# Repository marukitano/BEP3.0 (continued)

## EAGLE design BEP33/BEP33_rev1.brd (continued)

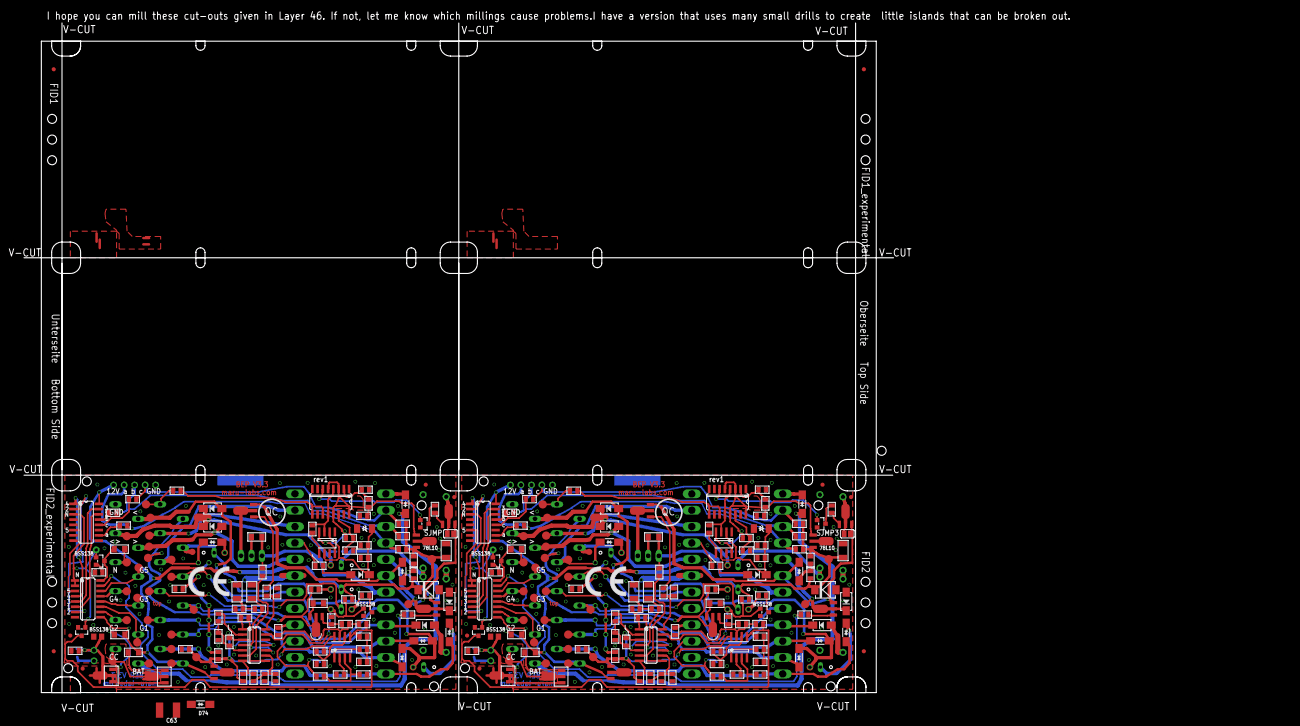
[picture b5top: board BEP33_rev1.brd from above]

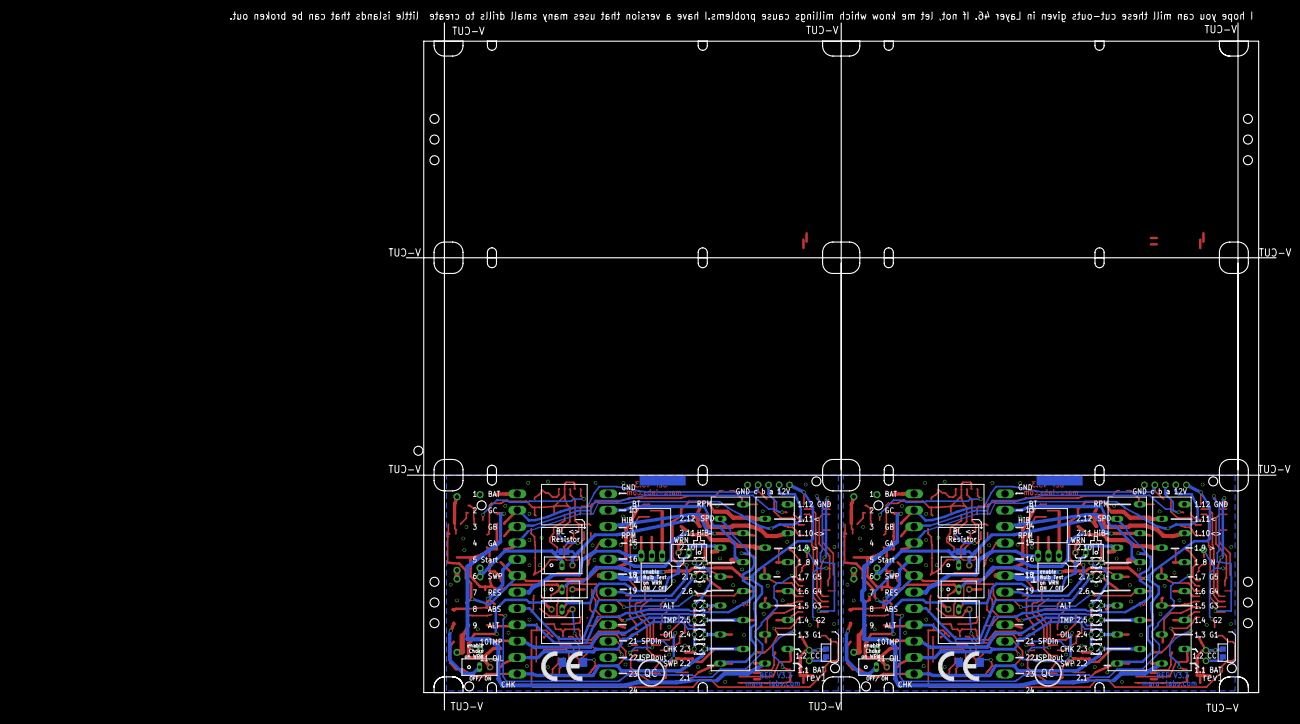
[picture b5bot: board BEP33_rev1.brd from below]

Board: 2 copper layers, 210.4 x 166.2 mm, 306 parts (50 on the bottom side), 181 nets.

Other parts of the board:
U$1, U$2, U$7, U$8: CE_10.00

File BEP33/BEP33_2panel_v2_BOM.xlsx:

Qty | Value | Device | Package | Parts | Description | MF | MPN | OC_FARNELL | OC_NEWARK | TP | TP_SIGNAL_NAME | VALUE
2 | 100nF | CERAMIC-100NF-50V-10%-X7R(0805) | C0805 | C102, C110 | 302010165 |  | CC0805KRX7R9BB104 |  |  |  |  | 10K
2 | 100nF, | CERAMIC-100NF-50V-10%-X7R(0805) | C0805 | C103, C104 | 302010165 |  | CC0805KRX7R9BB104 |  |  |  |  | 100R
2 | 100nF. | CERAMIC-100NF-50V-10%-X7R(0805) | C0805 | C105, C106 | 302010165 |  | CC0805KRX7R9BB104 |  |  |  |  | 2.2K
1 | 2.2nF | CERAMIC-100NF-50V-10%-X7R(0805) | C0805 | C109 | 302010165 |  | CC0805KRX7R9BB104 |  |  |  |  | 220R
2 | 4.7u | CERAMIC-4.7UF-25V-10%-X5R(0805) | C0805 | C15, C101 | 302010146 |  | CC0805KKX5R8BB475 |  |  |  |  | 10K
2 | 100u | CERAMIC-100UF-6.3V-20%-X5R(1206) | C1206 | C107, C108 | 302010183 |  | GRM31CR60J107ME39L |  |  |  |  | 1K
1 | 10u | CERAMIC-100UF-6.3V-20%-X5R(1206) | C1206 | C2 | 302010183 |  | GRM31CR60J107ME39L |  |  |  |  | 4.7K
1 | Zen15 | SM6T | DO214AA | D101 | Z DIODE |  |  |  |  |  |  | 100nf
1 | SM6TDO214AA_BI | SM6TDO214AA_BI | DO214AA_BI | D104 | Z DIODE |  |  |  |  |  |  | 100nf
1 | 1N4007 | DIODE-GEN-PURPOSE-1KV-1A(DO-214AC) | DO-214AC | D112 | 304010013 |  | 1N4007 |  |  |  |  | 100nf
2 | 1N4007, | DIODE-GEN-PURPOSE-1KV-1A(DO-214AC) | DO-214AC | D102, D103 | 304010013 |  | 1N4007 |  |  |  |  | 100uf
2 | 1N4007. | DIODE-GEN-PURPOSE-1KV-1A(DO-214AC) | DO-214AC | D105, D106 | 304010013 |  | 1N4007 |  |  |  |  | 1K
2 | 1N5817 | DIODE-GEN-PURPOSE-1KV-1A(DO-214AC)DO-214AC/1206 | DO-214AC_SLIM | D107, D110 | 304010013 |  |  |  |  |  |  | 220R
2 | 1N5817. | DIODE-GEN-PURPOSE-1KV-1A(DO-214AC)DO-214AC/1206 | DO-214AC_SLIM | D108, D109 | 304010013 |  |  |  |  |  |  | 10K
2 | SS12 | DIODE-GEN-PURPOSE-1KV-1A(DO-214AC)DO-214AC/1206 | DO-214AC_SLIM | D1, D2 | 304010013 |  |  |  |  |  |  | 4.7K
1 | -1000 | SMD-RES-100R-5%-1/8W(0805) | R0805 | R142 | 301010319 |  | RC0805JR-07100RL |  |  |  |  | 1N4007
1 | -1002 | SMD-RES-10K-1%-1/8W(0805) | R0805 | R144 | 301010361 |  | RC0805FR-0710KL |  |  |  |  | 1N4007
1 | -101 | SMD-RES-100R-5%-1/8W(0805) | R0805 | R143 | 301010319 |  | RC0805JR-07100RL
3 | 100 | SMD-RES-2.2K-5%-1/8W(0805) | R0805 | R12, R13, R138 | 301010333 |  | RC0805JR-072K2L
1 | 100 | SMD-RES-220R-5%-1/8W(0805) | R0805 | R4 | 301010315 |  | RC0805JR-07220RL |  |  |  |  | 100nf
5 | 1002 | SMD-RES-10K-1%-1/8W(0805) | R0805 | R107, R108, R120, R124, R132 | 301010361 |  | RC0805FR-0710KL
2 | 1002 | SMD-RES-1K-5%-1/8W(0805) | R0805 | R113, R114 | 301010311 |  | RC0805JR-071KL
1 | 1002 | SMD-RES-4.7K-5%-1/8W(0805) | R0805 | R146 | 301010306 |  | RC0805JR-074K7L |  |  |  |  | 1K
3 | 102 | SMD-RES-1K-5%-1/8W(0805) | R0805 | R101, R112, R128 | 301010311 |  | RC0805JR-071KL |  |  |  |  | 2.2K
1 | 102 | SMD-RES-220R-5%-1/8W(0805) | R0805 | R115 | 301010315 |  | RC0805JR-07220RL |  |  |  |  | 10K
10 | 104 | SMD-RES-10K-1%-1/8W(0805) | R0805 | R1, R2, R3, R109, R110, R111, R125, R130, R135, R141 | 301010361 |  | RC0805FR-0710KL |  |  |  |  | 4.7K
1 | 104 | SMD-RES-4.7K-5%-1/8W(0805) | R0805 | R10 | 301010306 |  | RC0805JR-074K7L
2 | 1502 | SMD-RES-10K-1%-1/8W(0805) | R0805 | R121, R131 | 301010361 |  | RC0805FR-0710KL |  |  |  |  | 4.7uf
1 | 2201 | SMD-RES-1K-5%-1/8W(0805) | R0805 | R6 | 301010311 |  | RC0805JR-071KL
2 | 2201 | SMD-RES-2.2K-5%-1/8W(0805) | R0805 | R119, R133 | 301010333 |  | RC0805JR-072K2L
1 | 2702 | SMD-RES-10K-1%-1/8W(0805) | R0805 | R140 | 301010361 |  | RC0805FR-0710KL
4 | 2702 | SMD-RES-4.7K-5%-1/8W(0805) | R0805 | R117, R122, R123, R145 | 301010306 |  | RC0805JR-074K7L |  |  |  |  | 4.7K
4 | 4701 | SMD-RES-4.7K-5%-1/8W(0805) | R0805 | R8, R105, R116, R126 | 301010306 |  | RC0805JR-074K7L
5 | 13 | SMD-RES-13R-5%-1/4W(1206) | R1206 | R5, R9, R102, R106, R134 | 301010405 |  | RC1206JR-0713RL
1 | 555 | NE555D | SO08 | IC110 | TIMER
1 | LM2904 | LM358D | SO08 | IC101 | OP AMP also LM158; LM258; LM2904
1 | LM339 | LM339D | SO14 | IC108 | Low Power Low Offset Voltage Quad Comparators |  |  |  |  |  |  | BSS138W-7-F
1 | 4028 | 4028D | SO16 | IC105 | BCD to decimal DECODER
1 | 4538 | 4538D | SO16 | IC111 | Dual precision monostable MULTIVIBRATOR
1 | ULN2004 | ULN2004AD | SO16 | IC107 | DRIVER ARRAY
1 | Zen11 | CGRM4001-G | SOD-123_MINI-SMA | D4 | Molded plasitc,JEDEC SOD-123/Mini SMA
4 | J1 | SMD-MOSFET-N-CH-50V-200MA-BSS138W-7-F(SOT-23) | SOT-23 | Q1, Q3, Q106, Q107 | 305030000 |  | BSS138W-7-F
3 | BA | PNP-TRANSISTOR_SOT89 | SOT89 | Q2, Q104, Q105 | PNP TRANSISTOR
2 | BA. | PNP-TRANSISTOR_SOT89 | SOT89 | Q101, Q102 | PNP TRANSISTOR
1 | MY | NPN-TRANSISTOR_SOT89 | SOT89 | Q103 | NPN TRANSISTOR
1 | 78L06 | 78LXXSOT89_ROUND | SOT89_ROUND | IC102
1 | 78L10 | 78LXXSOT89_ROUND | SOT89_ROUND | IC104
1 | 317TO202H_NOHOLE | 317TO202H_NOHOLE | TO220H_NOHOLE | IC109 | Positive VOLTAGE REGULATOR
4 | 47 | R-EU_V235/17_1MM | V235/17_1MM | R127, R129, R136, R137 | RESISTOR, European symbol

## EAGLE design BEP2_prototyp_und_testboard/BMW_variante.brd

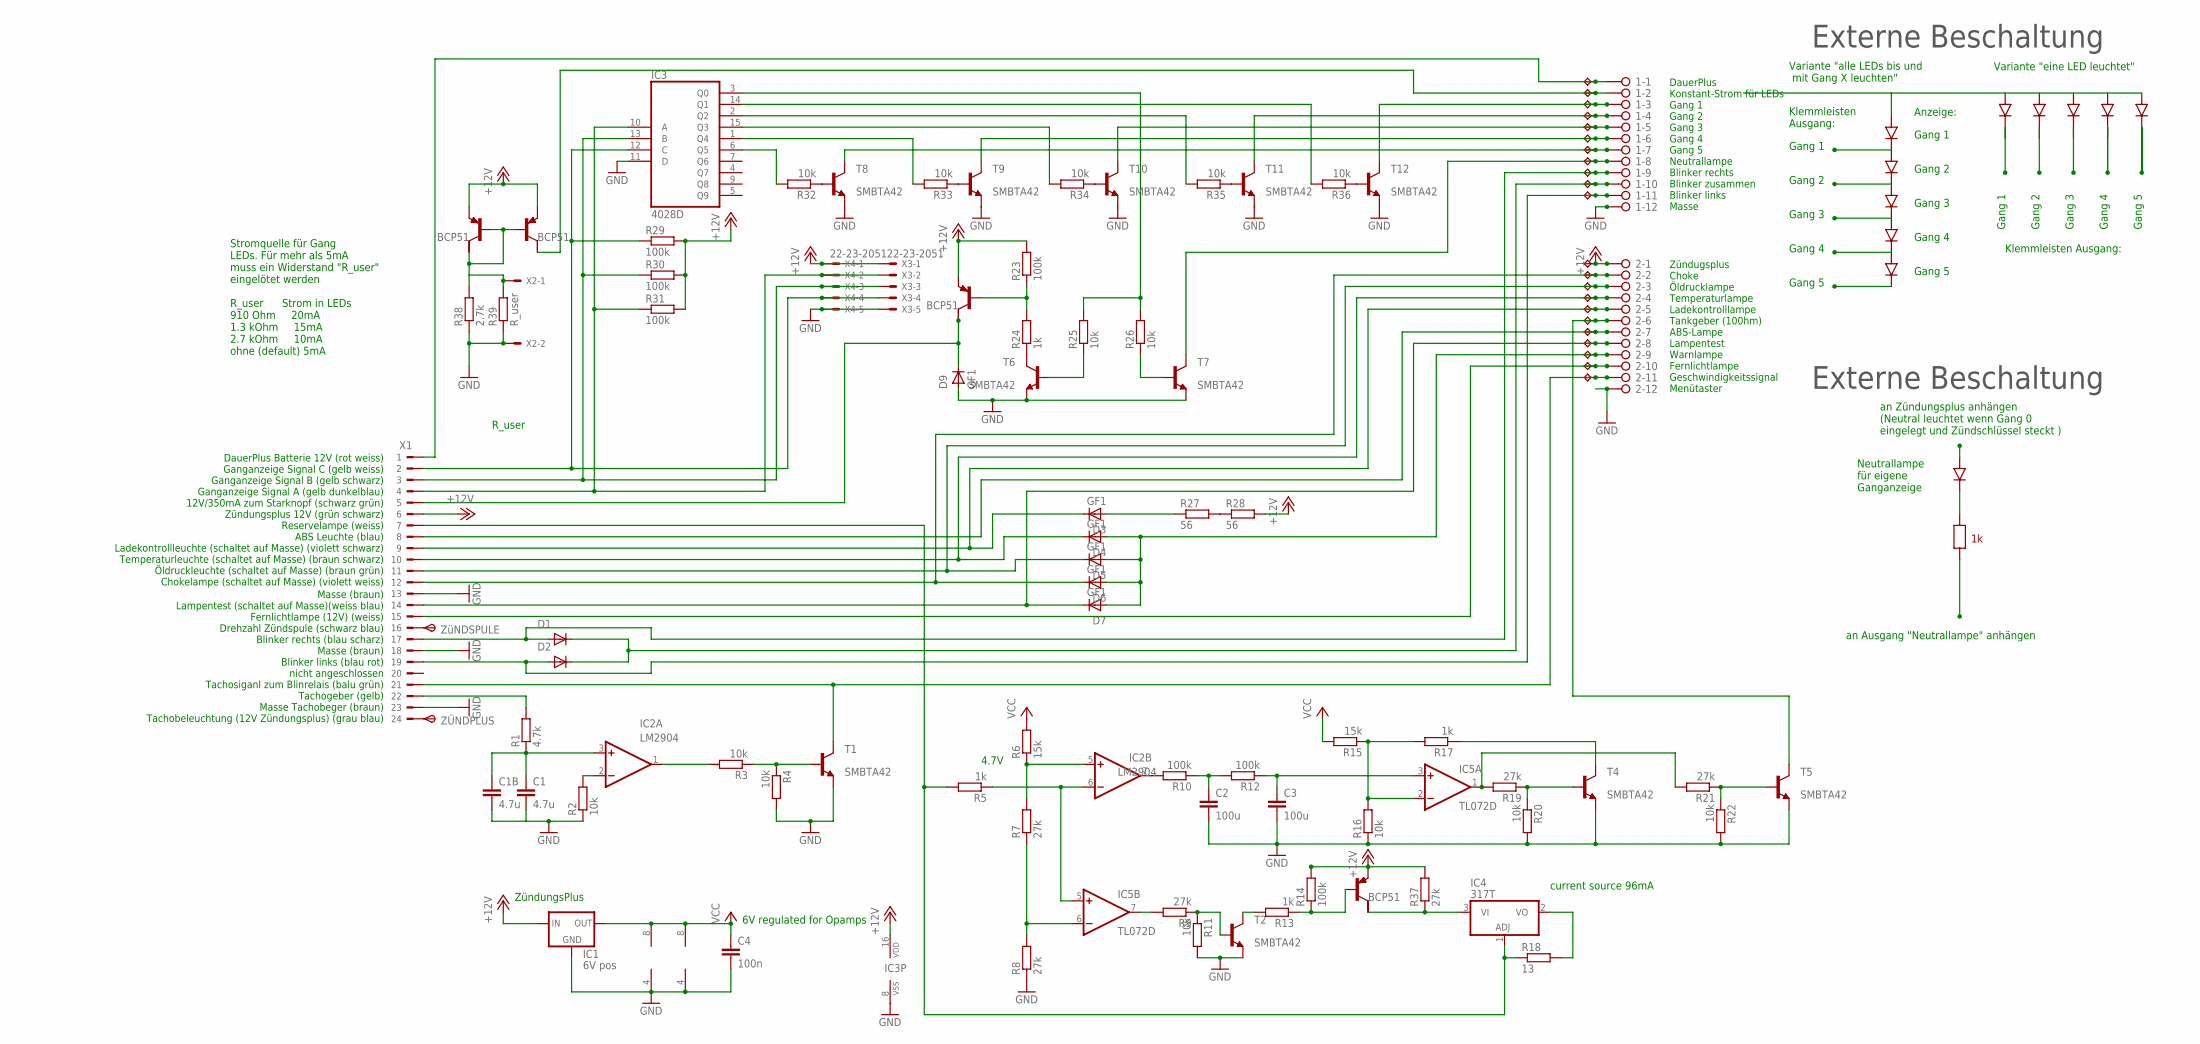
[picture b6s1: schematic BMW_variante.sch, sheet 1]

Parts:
1, 2: 2081-1132; 12-PIN
C1: 4.7u; C1206
C1B: 4.7u; C0805K
C2, C3: 100u; C1206K
C4: 100n; C1206K
D1, D2, D3, D4, D5, D6, D7, D9: GF1; SMA-DO214AC
IC1: 6V pos; 78LXX
IC2: LM358D; SO08
IC3: 4028D; SO16
IC4: 317T; TO220H
IC5: TL072D; SO08
R1: 4.7k; R0805
R2, R3, R4, R11, R16, R20, R22, R25, R26, R32, R33, R34, R35, R36: 10k; R0805
R5, R13, R17, R24: 1k; R0805
R6, R15: 15k; R0805
R7, R8, R9, R19, R21, R37: 27k; R0805
R10, R12, R14, R23, R29, R30, R31: 100k; R0805
R18: 13; 0207/10
R27, R28: 56; V235/17
R38: 2.7k; R0805
R39: R_user; R0805
T, T3, T13, T14: BCP53T1; SOT223
T1, T2, T4, T5, T6, T7, T8, T9, T10, T11, T12: MMBTA42LT1-NPN-SOT23-BEC; SOT23-BEC
TP1, TP2, TP3, TP4, TP5, TP6, TP7, TP8, TP9, TP10, TP11, TP12, TP16, TP17, TP18, TP19, TP21, TP22, TP23, TP24, TP25, TP26: TPB1,27; B1,27
X1: CON_BMW; 24-PIN
X2: 22-23-2021
X3, X4: 22-23-2051
ZÜNDPLUS: TPSP1_1MM; P1_1.0MM
ZüNDSPULE: TPSP1_1MM; P1_1.0MM

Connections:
+12V: 2.1, IC1.IN, IC3.16 (VDD), R14.2, R23.2, R28.2, R29.2, R30.2, R31.2, R37.2, T.3 (E), T3.3 (E), T13.3 (E), T14.3 (E), TP12.TP, X1.6, X3.1, X4.1
GND: 1.12, 2.12, C1.2, C1B.2, C2.2, C3.2, C4.2, D9.A, IC1.GND, IC2.4 (V-), IC3.8 (VSS), IC3.11 (D), IC5.4 (V-), R2.1, R4.2, R8.1, R11.2, R16.1, R20.2, R22.2, R38.1, R39.1, T1.E, T2.E, T4.E, T5.E, T6.E, T7.E, T8.E, T9.E, T10.E, T11.E, T12.E, X1.13, X1.18, X1.23, X2.2, X3.5, X4.5; also elsewhere on the board
unnamed: 2.9, D4.A, D5.A, D6.A, D7.A, TP24.TP
unnamed: IC3.10 (A), R31.1, X1.4, X3.2, X4.2
unnamed: IC3.13 (B), R30.1, X1.3, X3.3, X4.3
unnamed: 2.7, TP22.TP, X1.8
unnamed: R25.1, T6.B
unnamed: IC3.3 (Q0), R25.2, R26.2
unnamed: R24.1, T6.C
unnamed: R27.2, R28.1
unnamed: R23.1, R24.2, T.1 (B)
unnamed: R26.1, T7.B
unnamed: D9.K (C), T.2 (C), X1.5
unnamed: 2.2, D6.K (C), TP16.TP, X1.12
unnamed: 2.3, D5.K (C), TP17.TP, X1.11
unnamed: 2.4, D4.K (C), TP18.TP, X1.10
unnamed: IC4.1 (ADJ), R5.2, R18.1, X1.7
unnamed: IC2.6 (-IN), IC5.5 (+IN), R5.1
unnamed: IC3.12 (C), R29.1, X1.2, X3.4, X4.4
unnamed: R32.1, T8.B
unnamed: 2.8, D7.K (C), TP23.TP, X1.14
unnamed: 1.9, D1.A, TP9.TP, X1.17
unnamed: 1.11, D2.A, TP11.TP, X1.19
unnamed: 1.10, D1.K (C), D2.K (C), TP10.TP
unnamed: R1.2, X1.22
unnamed: C1.1, C1B.1, IC2.3 (+IN), R1.1
unnamed: IC2.2 (-IN), R2.2
unnamed: 2.11, T1.C, TP26.TP, X1.21
unnamed: IC2.1 (OUT), R3.2
unnamed: R3.1, R4.1, T1.B
unnamed: IC4.2 (VO), R18.2
unnamed: IC5.6 (-IN), R7.1, R8.2
unnamed: IC5.7 (OUT), R9.2
unnamed: R13.2, T2.C
unnamed: R9.1, R11.1, T2.B
unnamed: IC4.3 (VI), R37.1, T3.2 (C)
unnamed: R13.1, R14.1, T3.1 (B)
unnamed: IC3.14 (Q1), R36.2
unnamed: IC3.2 (Q2), R35.2
unnamed: 1.5, T10.C, TP5.TP
unnamed: IC2.5 (+IN), R6.1, R7.2
unnamed: IC2.7 (OUT), R10.2
unnamed: X1.16, ZüNDSPULE.TP
unnamed: IC5.1 (OUT), R19.2, R21.2
unnamed: R19.1, R20.1, T4.B
unnamed: C2.1, R10.1, R12.2
unnamed: C3.1, IC5.3 (+IN), R12.1
unnamed: IC5.2 (-IN), R15.1, R16.2, R17.2
unnamed: R21.1, R22.1, T5.B
unnamed: R17.1, T4.C
unnamed: 1.6, T9.C, TP6.TP
unnamed: R34.1, T10.B
unnamed: 1.8, T7.C, TP8.TP
unnamed: 2.10, TP25.TP, X1.15
unnamed: D3.A, R27.1
unnamed: 2.5, D3.K (C), TP19.TP, X1.9
unnamed: R33.1, T9.B
unnamed: R35.1, T11.B
unnamed: X1.24, ZÜNDPLUS.TP
unnamed: 1.2, T14.2 (C), TP2.TP
unnamed: 2.6, T5.C, TP21.TP
unnamed: IC3.6 (Q5), R32.2
unnamed: R36.1, T12.B
unnamed: 1.7, T8.C, TP7.TP
unnamed: IC3.1 (Q4), R33.2
unnamed: IC3.15 (Q3), R34.2
unnamed: 1.4, T11.C, TP4.TP
unnamed: 1.3, T12.C, TP3.TP
unnamed: R38.2, R39.2, T13.1 (B), T13.2 (C), T14.1 (B), X2.1
unnamed: 1.1, TP1.TP, X1.1
VCC: C4.1, IC1.OUT, IC2.8 (V+), IC5.8 (V+), R6.2, R15.2; also elsewhere on the board

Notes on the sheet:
6V regulated for Opamps
current source 96mA
ZündungsPlus
Zündugsplus Choke Öldrucklampe Temperaturlampe Ladekontrolllampe Tankgeber (100hm) ABS-Lampe Lampentest Warnlampe Fernlichtlampe Geschwindigkeitssignal Menütaster
DauerPlus Konstant-Strom für LEDs Gang 1 Gang 2 Gang 3 Gang 4 Gang 5 Neutrallampe Blinker rechts Blinker zusammen Blinker links Masse
DauerPlus Batterie 12V (rot weiss) Ganganzeige Signal C (gelb weiss) Ganganzeige Signal B (gelb schwarz) Ganganzeige Signal A (gelb dunkelblau) 12V/350mA zum Starknopf (schwarz grün) Zündungsplus 12V (grün schwarz) Reservelampe (weiss) ABS Leuchte (blau) Ladekontrollleuchte (schaltet auf Masse) (vi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
Masse (braun) Lampentest (schaltet auf Masse)(weiss blau) Fernlichtlampe (12V) (weiss) Drehzahl Zündspule (schwarz blau) Blinker rechts (blau scharz) Masse (braun) Blinker links (blau rot) nicht angeschlossen Tachosiganl zum Blinrelais (balu grün) Tachogeber (gelb) Masse Tachobeger (braun) Tachobel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
4.7V
Stromquelle für Gang LEDs. Für mehr als 5mA muss ein Widerstand "R_user" eingelötet werden R_user Strom in LEDs 910 Ohm 20mA 1.3 kOhm 15mA 2.7 kOhm 10mA ohne (default) 5mA
R_user
Gang 1
Gang 2
Gang 3
Gang 4
Gang 5
Variante "eine LED leuchtet"
Variante "alle LEDs bis und mit Gang X leuchten"
Klemmleisten Ausgang:
Klemmleisten Ausgang:
an Zündungsplus anhängen (Neutral leuchtet wenn Gang 0 eingelegt und Zündschlüssel steckt )
an Ausgang "Neutrallampe" anhängen
Neutrallampe für eigene Ganganzeige
Externe Beschaltung
Anzeige:

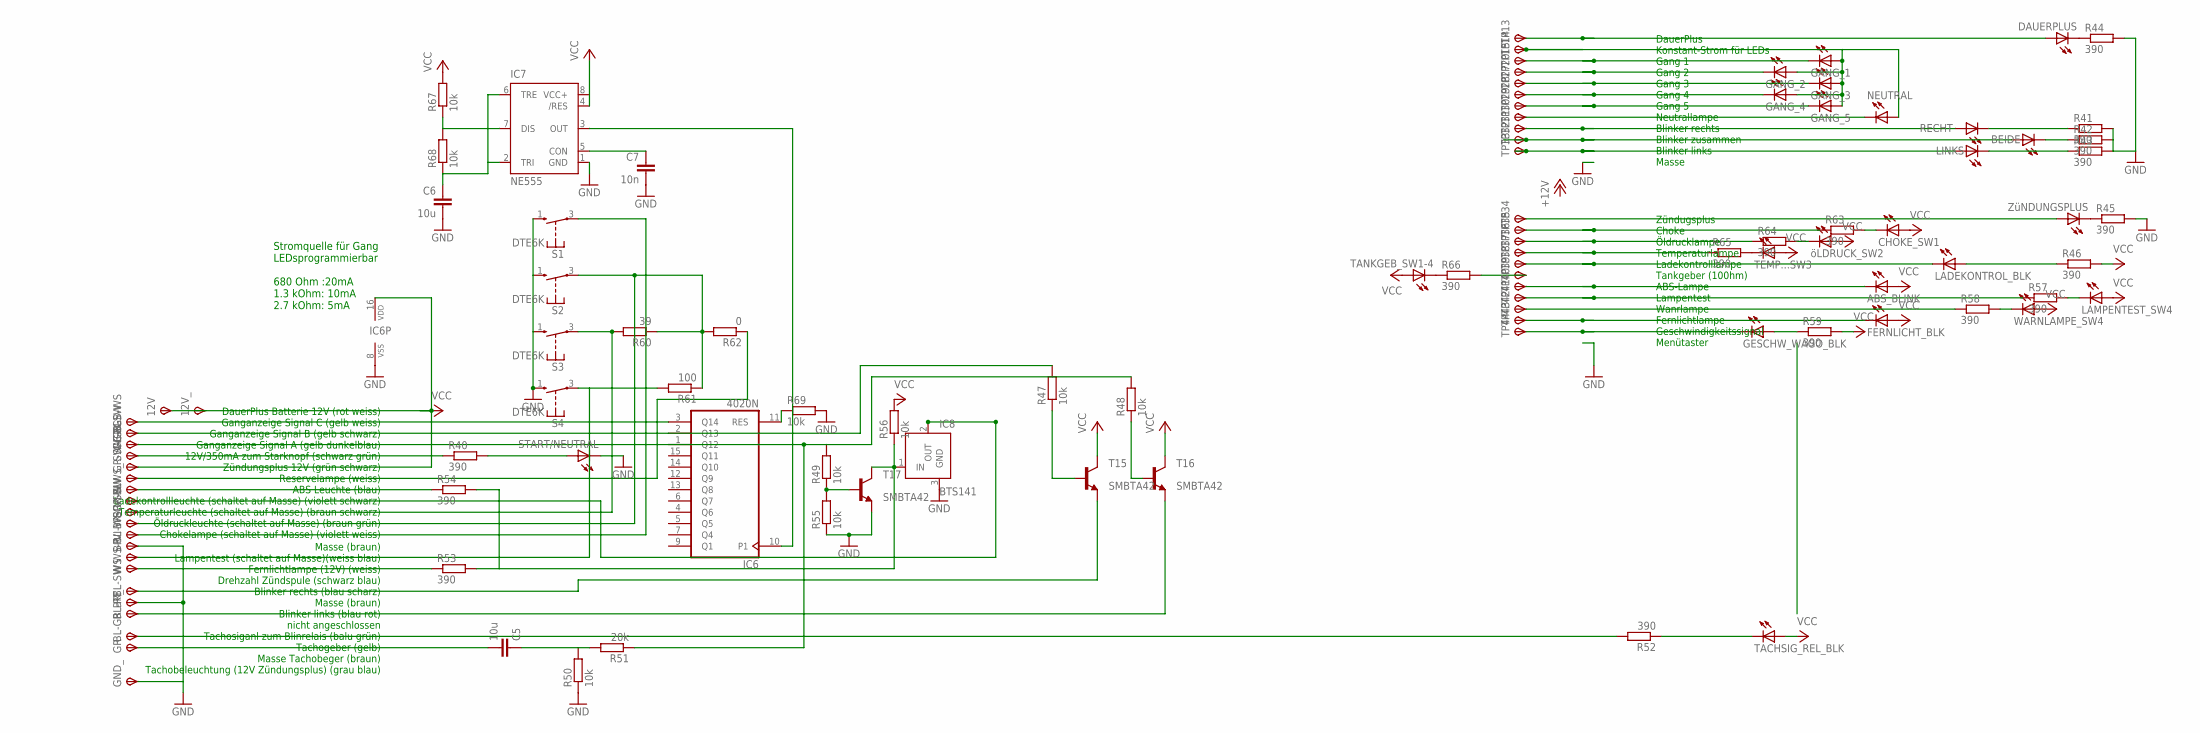
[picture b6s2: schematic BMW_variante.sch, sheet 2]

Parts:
12V, 12V_: TPSPAD1-1.5MM; P1-13
ABS_BLINK: TLLY4400; LED3MM
BEIDE: TLLY4400; LED3MM
BL: TPSPAD1-1.5MM; P1-13
BL-GR: TPSPAD1-1.5MM; P1-13
BL-RT: TPSPAD1-1.5MM; P1-13
BL-SW: TPSPAD1-1.5MM; P1-13
BR: TPSPAD1-1.5MM; P1-13
BR-GR: TPSPAD1-1.5MM; P1-13
BR-SW: TPSPAD1-1.5MM; P1-13
BR_: TPSPAD1-1.5MM; P1-13
C5, C6: 10u; C025-024X044
C7: 10n; C025-024X044
CHOKE_SW1: TLLY4400; LED3MM
DAUERPLUS: TLLY4400; LED3MM
FERNLICHT_BLK: TLLY4400; LED3MM
GANG_1, GANG_2, GANG_3, GANG_4, GANG_5: TLLY4400; LED3MM
GB-SW: TPSPAD1-1.5MM; P1-13
GB-WS: TPSPAD1-1.5MM; P1-13
GE-BL: TPSPAD1-1.5MM; P1-13
GESCHW_WAGO_BLK: TLLY4400; LED3MM
GND_: TPSPAD1-1.5MM; P1-13
GR: TPSPAD1-1.5MM; P1-13
GR-SW: TPSPAD1-1.5MM; P1-13
IC6: 4020N; DIL16
IC7: NE555; DIL-08
IC8: BTS141; TO220-3-45
LADEKONTROL_BLK: TLLY4400; LED3MM
LAMPENTEST_SW4: TLLY4400; LED3MM
LINKS: TLLY4400; LED3MM
NEUTRAL: TLLY4400; LED3MM
R40, R41, R42, R43, R44, R45, R46, R52, R53, R54, R57, R58, R59, R63, R64, R65, R66: 390; R0805
R47, R48, R49, R55, R56, R69: 10k; R0805
R50, R67: 10k; 0207/12
R51: 20k; 0207/12
R60: 39; 0207/12
R61: 100; 0207/12
R62: 0; 0207/12
R68: 10k; 0207/15
RECHT: TLLY4400; LED3MM
S1, S2, S3, S4: DTE6K
START/NEUTRAL: TLLY4400; LED3MM
SW-GR: TPSPAD1-1.5MM; P1-13
T15, T16, T17: MMBTA42LT1-NPN-SOT23-BEC; SOT23-BEC
TACHSIG_REL_BLK: TLLY4400; LED3MM
TANKGEB_SW1-4: TLLY4400; LED3MM
TEMP...SW3: TLLY4400; LED3MM
TP13, TP14, TP15, TP20, TP27, TP28, TP29, TP30, TP31, TP32, TP33, TP34, TP35, TP36, TP37, TP38, TP39, TP40, TP41, TP42, TP43, TP44: TPSPAD1-1.5MM; P1-13
VI-SW: TPSPAD1-1.5MM; P1-13
VI-WS: TPSPAD1-1.5MM; P1-13
WARNLAMPE_SW4: TLLY4400; LED3MM
WS: TPSPAD1-1.5MM; P1-13
WS-BL: TPSPAD1-1.5MM; P1-13
WS_: TPSPAD1-1.5MM; P1-13
ZüNDUNGSPLUS: TLLY4400; LED3MM
öLDRUCK_SW2: TLLY4400; LED3MM

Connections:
GND: BR.TP, BR_.TP, C6.2, C7.2, GND_.TP, IC6.8 (VSS), IC7.1 (GND), IC8.3 (GND), R41.2, R42.2, R43.2, R44.2, R45.2, R50.1, R55.1, R69.2, S1.1 (S), S2.1 (S), S3.1 (S), S4.1 (S), START/NEUTRAL.K (C), T17.E; also elsewhere on the board
unnamed: R58.1, TP42.TP
unnamed: ABS_BLINK.K (C), TP40.TP
unnamed: R64.1, TP36.TP
unnamed: R65.1, TP37.TP
unnamed: R57.1, TP41.TP
unnamed: RECHT.A, TP31.TP
unnamed: LINKS.A, TP33.TP
unnamed: BEIDE.A, TP32.TP
unnamed: GESCHW_WAGO_BLK.K (C), TP44.TP
unnamed: NEUTRAL.K (C), TP30.TP
unnamed: GANG_5.K (C), TP29.TP
unnamed: GANG_1.A, GANG_2.A, GANG_3.A, GANG_4.A, GANG_5.A, NEUTRAL.A, TP14.TP
unnamed: DAUERPLUS.A, TP13.TP
unnamed: GANG_3.K (C), TP27.TP
unnamed: GANG_4.K (C), TP28.TP
unnamed: R66.2, TP39.TP
unnamed: GANG_2.K (C), TP20.TP
unnamed: GANG_1.K (C), TP15.TP
unnamed: GB-WS.TP, IC6.3 (Q14)
unnamed: GB-SW.TP, IC6.2 (Q13), R47.2
unnamed: LADEKONTROL_BLK.K (C), TP38.TP
unnamed: R40.2, START/NEUTRAL.A
unnamed: R40.1, SW-GR.TP
unnamed: IC8.1 (IN), R53.2, R54.2, R56.1, T17.C
unnamed: R41.1, RECHT.K (C)
unnamed: BEIDE.K (C), R42.1
unnamed: LINKS.K (C), R43.1
unnamed: DAUERPLUS.K (C), R44.1
unnamed: R45.1, ZüNDUNGSPLUS.K (C)
unnamed: FERNLICHT_BLK.K (C), TP43.TP
unnamed: R47.1, T15.B
unnamed: R48.1, T16.B
unnamed: BL-SW.TP, T15.E
unnamed: BL-RT.TP, T16.E
unnamed: R49.1, R55.2, T17.B
unnamed: C5.1, R50.2, R51.2
unnamed: C5.2, GR.TP
unnamed: R52.1, TACHSIG_REL_BLK.K (C)
unnamed: BL-GR.TP, R52.2
unnamed: GE-BL.TP, IC6.1 (Q12), R48.2, R49.2, R51.1
unnamed: R53.1, WS.TP
unnamed: BL.TP, R54.1
unnamed: LADEKONTROL_BLK.A, R46.1
unnamed: IC8.2 (OUT), VI-SW.TP
unnamed: R58.2, WARNLAMPE_SW4.K (C)
unnamed: LAMPENTEST_SW4.K (C), R57.2
unnamed: GESCHW_WAGO_BLK.A, R59.1
unnamed: BR-GR.TP, R60.1, R61.1, R62.2, S2.3
unnamed: R61.2, S4.3, WS-BL.TP
unnamed: BR-SW.TP, R60.2, S3.3
unnamed: R63.1, TP35.TP
unnamed: R64.2, öLDRUCK_SW2.K (C)
unnamed: CHOKE_SW1.K (C), R63.2
unnamed: R65.2, TEMP...SW3.K (C)
unnamed: R66.1, TANKGEB_SW1-4.K (C)
unnamed: C6.1, IC7.2 (TRI), IC7.6 (TRE), R68.1
unnamed: IC7.7 (DIS), R67.1, R68.2
unnamed: C7.1, IC7.5 (CON)
unnamed: IC6.10 (P1), IC7.3 (OUT)
unnamed: TP34.TP, ZüNDUNGSPLUS.A
unnamed: IC6.11 (RES), R69.1
VCC: 12V.TP, 12V_.TP, ABS_BLINK.A, CHOKE_SW1.A, FERNLICHT_BLK.A, GR-SW.TP, IC6.16 (VDD), IC7.4 (/RES), IC7.8 (VCC+), LAMPENTEST_SW4.A, R46.2, R56.2, R59.2, R67.2, T15.C, T16.C, TACHSIG_REL_BLK.A, TANKGEB_SW1-4.A, TEMP...SW3.A, WARNLAMPE_SW4.A, öLDRUCK_SW2.A; also elsewhere on the board
VI-WS: S1.3, VI-WS.TP
WS: R62.1, WS_.TP

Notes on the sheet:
Zündugsplus Choke Öldrucklampe Temperaturlampe Ladekontrolllampe Tankgeber (100hm) ABS-Lampe Lampentest Wanrlampe Fernlichtlampe Geschwindigkeitssignal Menütaster
DauerPlus Konstant-Strom für LEDs Gang 1 Gang 2 Gang 3 Gang 4 Gang 5 Neutrallampe Blinker rechts Blinker zusammen Blinker links Masse
DauerPlus Batterie 12V (rot weiss) Ganganzeige Signal C (gelb weiss) Ganganzeige Signal B (gelb schwarz) Ganganzeige Signal A (gelb dunkelblau) 12V/350mA zum Starknopf (schwarz grün) Zündungsplus 12V (grün schwarz) Reservelampe (weiss) ABS Leuchte (blau) Ladekontrollleuchte (schaltet auf Masse) (vi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
Masse (braun) Lampentest (schaltet auf Masse)(weiss blau) Fernlichtlampe (12V) (weiss) Drehzahl Zündspule (schwarz blau) Blinker rechts (blau scharz) Masse (braun) Blinker links (blau rot) nicht angeschlossen Tachosiganl zum Blinrelais (balu grün) Tachogeber (gelb) Masse Tachobeger (braun) Tachobel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
Stromquelle für Gang LEDsprogrammierbar 680 Ohm :20mA 1.3 kOhm: 10mA 2.7 kOhm: 5mA

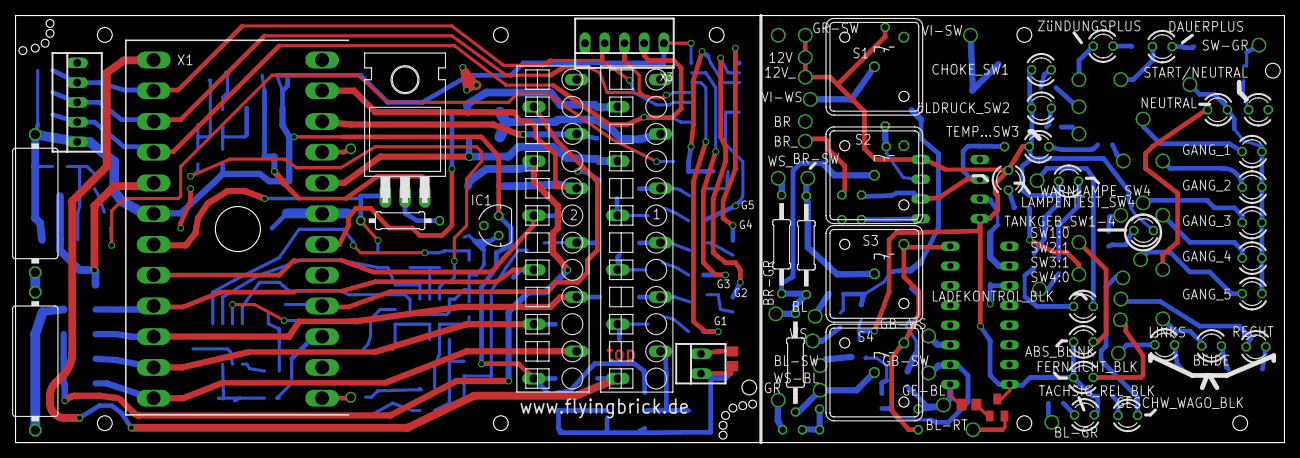
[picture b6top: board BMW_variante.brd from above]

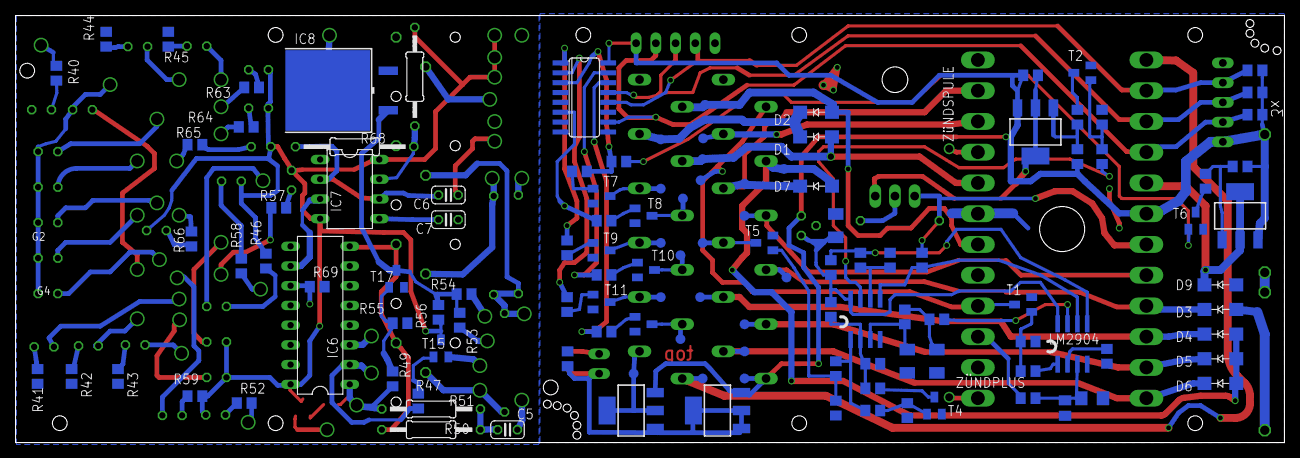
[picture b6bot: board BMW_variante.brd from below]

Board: 2 copper layers, 163.4 x 55.0 mm, 212 parts (146 on the bottom side), 134 nets.

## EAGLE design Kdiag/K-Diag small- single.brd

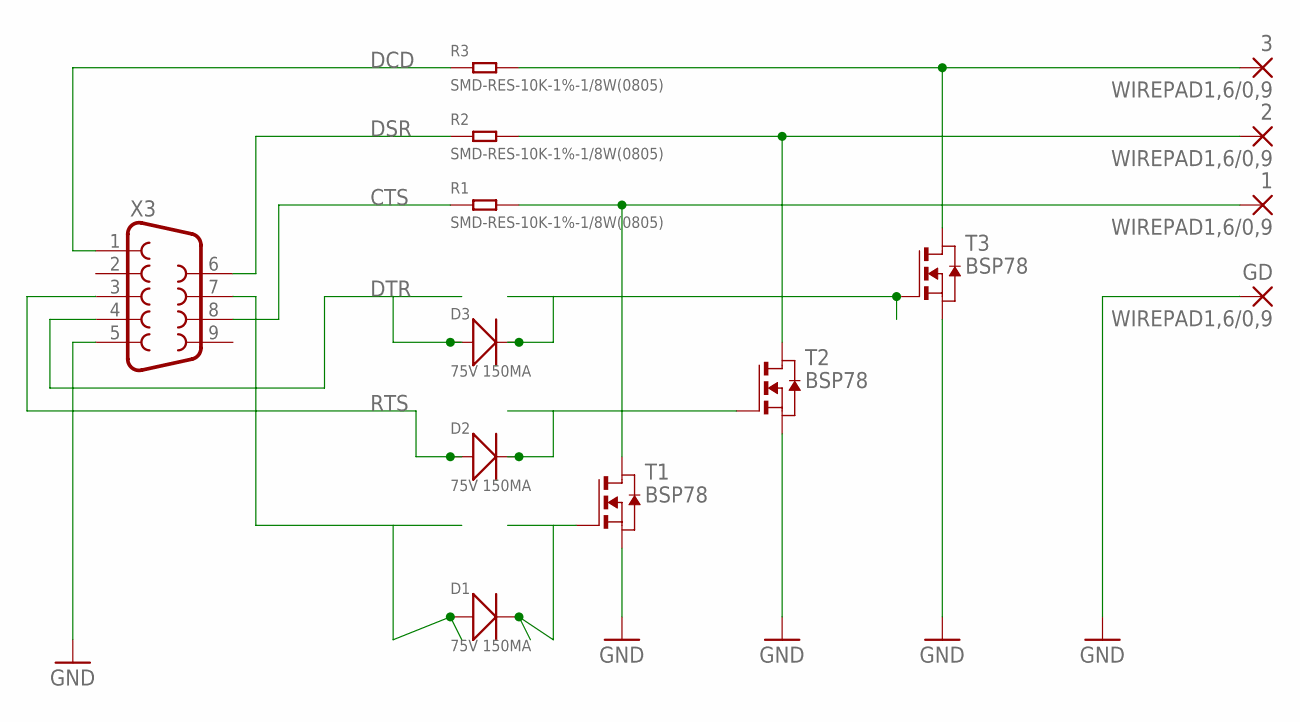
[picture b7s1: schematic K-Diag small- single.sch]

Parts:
1, 2, 3: WIREPAD1,6/0,9; 1,6/0,9
D1, D2, D3: 75V 150MA; LED-1206
GD: WIREPAD1,6/0,9; 1,6/0,9
R1, R2, R3: SMD-RES-10K-1%-1/8W(0805); R0805
T1, T2, T3: BSP78; SOT223
X3: F09D

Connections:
CTS: R1.1, X3.8
DCD: R3.1, X3.1
DSR: R2.1, X3.6
DTR: D3.+, X3.4
GND: GD.1, T1.3 (S), T2.3 (S), T3.3 (S), X3.5
unnamed: D3.-, T3.1 (G)
unnamed: D2.-, T2.1 (G)
unnamed: D1.-, T1.1 (G)
unnamed: 1.1, R1.2, T1.2 (D), T1.4 (D)
unnamed: 2.1, R2.2, T2.2 (D), T2.4 (D)
unnamed: 3.1, R3.2, T3.2 (D), T3.4 (D)
unnamed: D1.+, X3.7
RTS: D2.+, X3.3

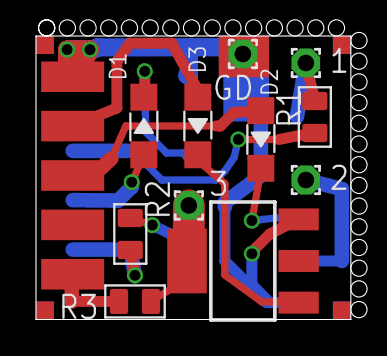
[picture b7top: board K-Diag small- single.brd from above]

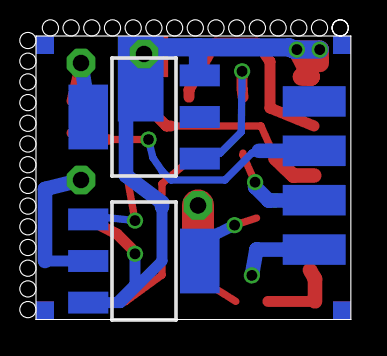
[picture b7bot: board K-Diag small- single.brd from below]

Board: 2 copper layers, 17.5 x 15.8 mm, 14 parts (2 on the bottom side), 13 nets.

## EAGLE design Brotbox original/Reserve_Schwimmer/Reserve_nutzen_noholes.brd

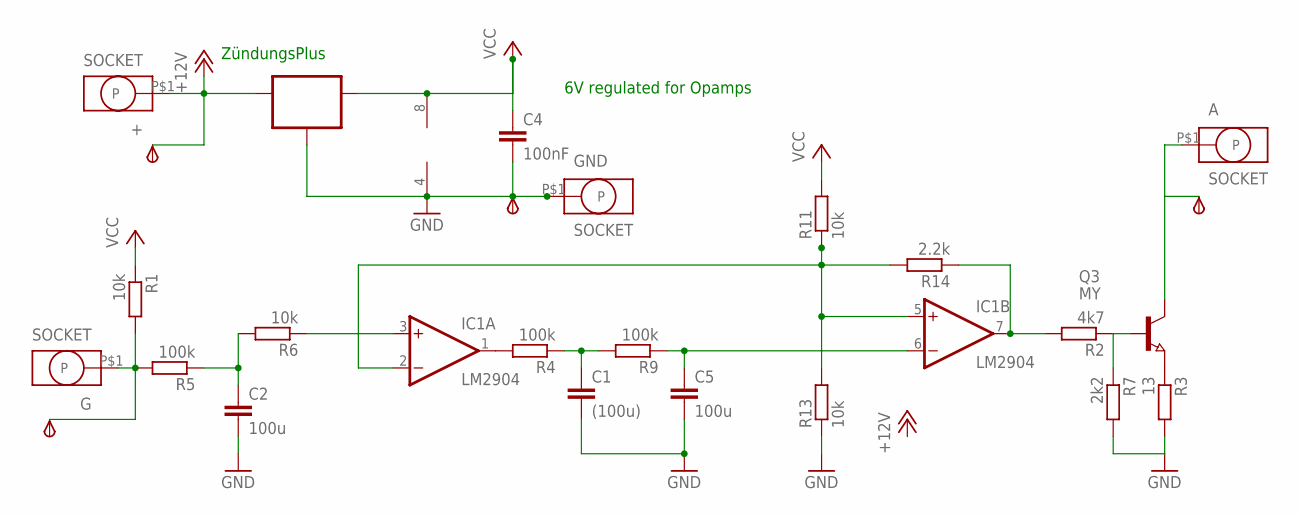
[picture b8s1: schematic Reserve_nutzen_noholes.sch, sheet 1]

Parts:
+: SOCKET; ID2.5MM
A: SOCKET; ID2.5MM
C1: (100u); C1206K
C2, C5: 100u; C1206K
C4: 100nF; C0805
G: SOCKET; ID2.5MM
GND: SOCKET; ID2.5MM
GND_: TPSB2.0; B2.0
IC1: LM2904; SO08
IC2: 70L06; SOT89_ROUND
IN: TPSB2.0; B2.0
OUT: TPSB2.0; B2.0
Q3: MY; SOT89
R1, R6, R11, R13: 10k; R0805
R2: 4k7; R0805
R3: 13; R1206
R4, R5, R9: 100k; R0805
R7: 2k2; R0805
R14: 2.2k; R0805
V+: TPSB2.0; B2.0

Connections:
+12V: +.P$1, IC2.3 (IN), V+.TP
GND: C1.2, C2.2, C4.2, C5.2, GND.P$1, GND_.TP, IC1.4 (V-), IC2.2 (GND), IC2.2@1 (GND), R3.2, R7.2, R13.1
unnamed: C2.1, R5.1, R6.2
unnamed: Q3.1 (B), R2.1, R7.1
unnamed: C1.1, R4.1, R9.2
unnamed: C5.1, IC1.6 (-IN), R9.1
unnamed: IC1.2 (-IN), IC1.5 (+IN), R11.1, R13.2, R14.2
unnamed: G.P$1, IN.TP, R1.2, R5.2
unnamed: Q3.3 (E), R3.1
unnamed: IC1.3 (+IN), R6.1
unnamed: IC1.7 (OUT), R2.2, R14.1
unnamed: A.P$1, OUT.TP, Q3.2 (C)
unnamed: IC1.1 (OUT), R4.2
VCC: C4.1, IC1.8 (V+), IC2.1 (OUT), R1.1, R11.2

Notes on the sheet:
6V regulated for Opamps
ZündungsPlus

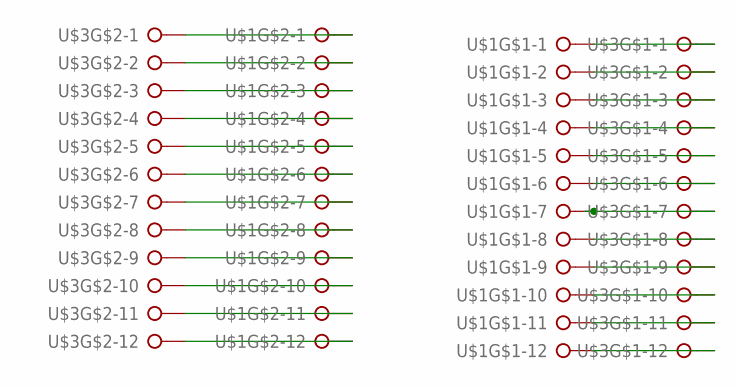
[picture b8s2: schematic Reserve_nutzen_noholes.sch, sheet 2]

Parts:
U$1: TESTADAPTER-24P; 24-PIN-TESTADAPTER
U$3: TESTADAPTER-24P24-PIN-ANSCHLUSS; 24-PIN-ANSCHLUSS

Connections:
unnamed: U$1.P$2-1, U$3.P$2-1
unnamed: U$1.P$2-2, U$3.P$2-2
unnamed: U$1.P$2-3, U$3.P$2-3
unnamed: U$1.P$2-4, U$3.P$2-4
unnamed: U$1.P$2-5, U$3.P$2-5
unnamed: U$1.P$2-6, U$3.P$2-6
unnamed: U$1.P$2-7, U$3.P$2-7
unnamed: U$1.P$2-8, U$3.P$2-8
unnamed: U$1.P$2-9, U$3.P$2-9
unnamed: U$1.P$2-10, U$3.P$2-10
unnamed: U$1.P$2-11, U$3.P$2-11
unnamed: U$1.P$2-12, U$3.P$2-12
unnamed: U$1.P$1-2, U$3.P$1-2
unnamed: U$1.P$1-3, U$3.P$1-3
unnamed: U$1.P$1-4, U$3.P$1-4
unnamed: U$1.P$1-6, U$3.P$1-6
unnamed: U$1.P$1-7, U$3.P$1-7
unnamed: U$1.P$1-8, U$3.P$1-8
unnamed: U$1.P$1-9, U$3.P$1-9
unnamed: U$1.P$1-10, U$3.P$1-10
unnamed: U$1.P$1-11, U$3.P$1-11
unnamed: U$1.P$1-12, U$3.P$1-12
unnamed: U$1.P$1-5, U$3.P$1-5
unnamed: U$1.P$1-1, U$3.P$1-1
